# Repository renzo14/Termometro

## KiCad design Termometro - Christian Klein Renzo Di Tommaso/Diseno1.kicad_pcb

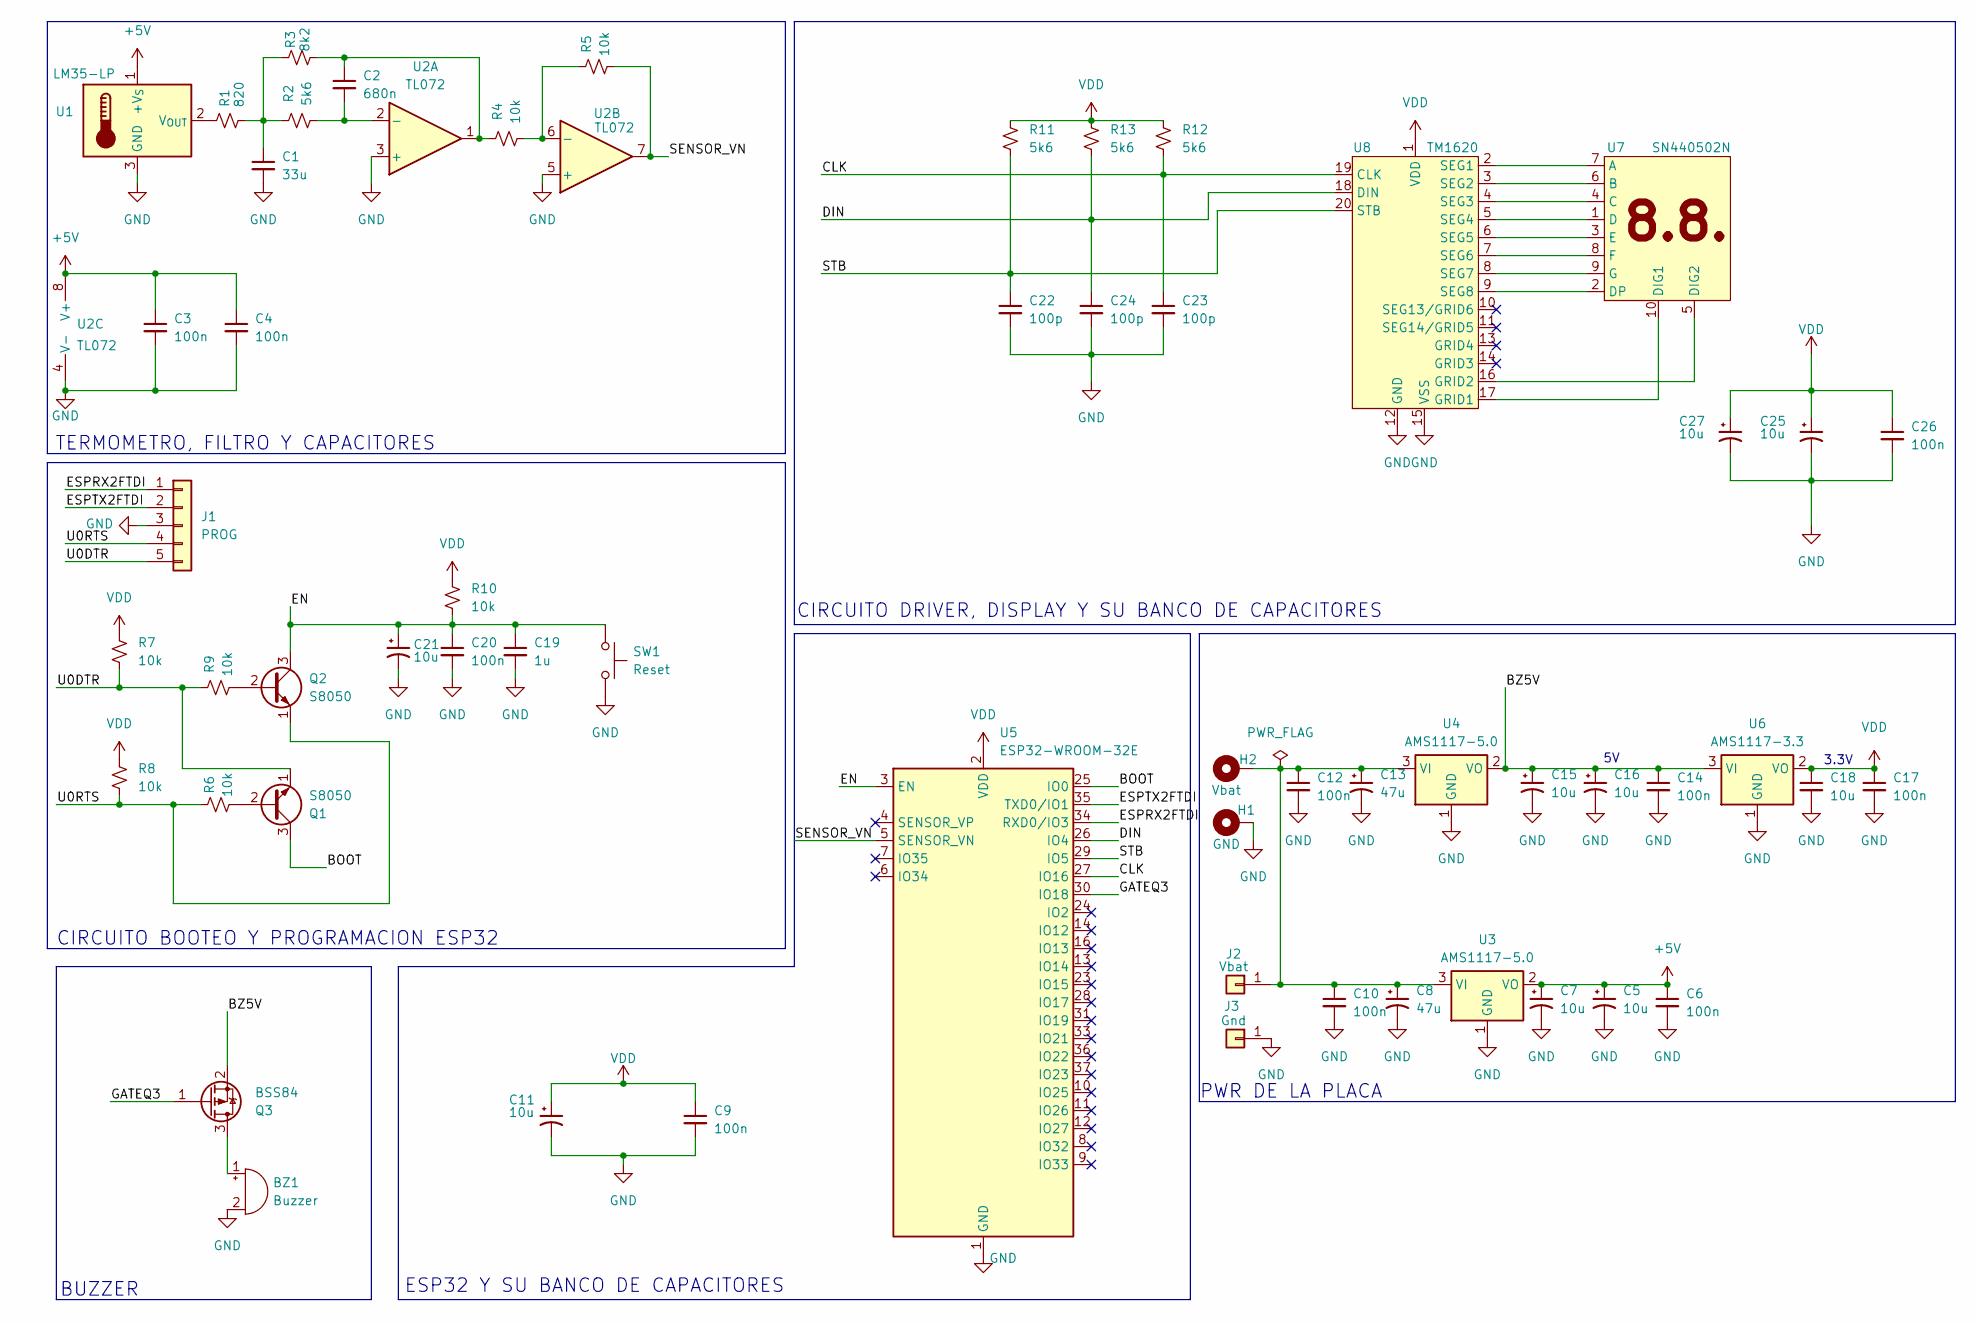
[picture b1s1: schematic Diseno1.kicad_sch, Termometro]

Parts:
BZ1: Buzzer; Buzzer_12x9.5RM7.6
C1: 33u; C_0805_2012Metric
C2: 680n; C_0603_1608Metric
C3, C4, C6, C9, C10, C12, C14, C17, C20, C26: 100n; C_0603_1608Metric
C5, C7, C11, C15, C16, C18, C21, C25, C27: 10u; C_0603_1608Metric
C8, C13: 47u; C_0805_2012Metric
C19: 1u; C_0603_1608Metric
C22, C23, C24: 100p; C_0603_1608Metric
H1: GND; MountingHole_2.2mm_M2_ISO7380_Pad
H2: Vbat; MountingHole_2.2mm_M2_ISO7380_Pad
J1: PROG; PinHeader_1x05_P2.54mm_Vertical
J2: Vbat; PinHeader_1x01_P2.54mm_Vertical
J3: Gnd; PinHeader_1x01_P2.54mm_Vertical
Q1, Q2: S8050; SOT-23
Q3: BSS84; SOT-23
R1: 820; R_0603_1608Metric
R2, R11, R12, R13: 5k6; R_0603_1608Metric
R3: 8k2; R_0603_1608Metric
R4, R5, R6, R7, R8, R9, R10: 10k; R_0603_1608Metric
SW1: Reset; SW_SPST_PTS645
U1: LM35-LP; TO-92_Inline
U2: TL072; SOIC-8_3.9x4.9mm_P1.27mm
U3, U4: AMS1117-5.0; SOT-223
U5: ESP32-WROOM-32E; ESP32-WROOM-32D
U6: AMS1117-3.3; SOT-223
U7: SN440502N; DISPLAYLEDS
U8: TM1620; SOIC-20W_7.5x12.8mm_P1.27mm

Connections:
+5V: C3.1, C4.1, C5.1, C6.1, C7.1, U1.1 (+V_{S}), U2.8 (V+), U3.2 (VO)
/BOOT: Q1.3 (C), U5.25 (IO0)
/BZ: C14.1, C15.1, C16.1, Q3.2 (S), U4.2 (VO), U6.3 (VI)
/CLK: C23.1, R12.1, U5.27 (IO16), U8.19 (CLK)
/DIN: C24.1, R13.1, U5.26 (IO4), U8.18 (DIN)
/EN: C19.1, C20.1, C21.1, Q2.3 (C), R10.1, SW1.1, U5.3 (EN)
/ESPRX2FTDI: J1.1, U5.34 (RXD0/IO3)
/ESPTX2FTDI: J1.2, U5.35 (TXD0/IO1)
/GATEQ3: Q3.1 (G), U5.30 (IO18)
/SENSOR_VN: R5.2, U2.7, U5.5 (SENSOR_VN)
/STB: C22.1, R11.1, U5.29 (IO5), U8.20 (STB)
/U0DTR: J1.5, Q1.1 (E), R7.1, R9.1
/U0RTS: J1.4, Q2.1 (E), R6.1, R8.1
GND: BZ1.2 (-), C1.2, C3.2, C4.2, C5.2, C6.2, C7.2, C8.2, C9.2, C10.2, C11.2, C12.2, C13.2, C14.2, C15.2, C16.2, C17.2, C18.2, C19.2, C20.2, C21.2, C22.2, C23.2, C24.2, C25.2, C26.2, C27.2, H1.1, J1.3, J3.1, SW1.2, U1.3 (GND), U2.3 (+), U2.4 (V-), U2.5 (+), U3.1 (GND), U4.1 (GND), U5.1 (GND), U5.15 (GND), U5.38 (GND), U5.39 (GND), U6.1 (GND), U8.12 (GND), U8.15 (VSS)
unnamed: BZ1.1 (+), Q3.3 (D)
unnamed: C1.1, R1.2, R2.1, R3.1
unnamed: C2.1, R3.2, R4.1, U2.1
unnamed: C8.1, C10.1, C12.1, C13.1, H2.1, J2.1, U3.3 (VI), U4.3 (VI)
unnamed: Q1.2 (B), R6.2
unnamed: Q2.2 (B), R9.2
unnamed: R1.1, U1.2 (V_{OUT})
unnamed: C2.2, R2.2, U2.2 (-)
unnamed: R4.2, R5.1, U2.6 (-)
unnamed: U7.7 (A), U8.2 (SEG1)
unnamed: U7.6 (B), U8.3 (SEG2)
unnamed: U7.4 (C), U8.4 (SEG3)
unnamed: U7.1 (D), U8.5 (SEG4)
unnamed: U7.10 (DIG1), U8.17 (GRID1)
unnamed: U7.5 (DIG2), U8.16 (GRID2)
unnamed: U7.2 (DP), U8.9 (SEG8)
unnamed: U7.3 (E), U8.6 (SEG5)
unnamed: U7.8 (F), U8.7 (SEG6)
unnamed: U7.9 (G), U8.8 (SEG7)
VDD: C9.1, C11.1, C17.1, C18.1, C25.1, C26.1, C27.1, R7.2, R8.2, R10.2, R11.2, R12.2, R13.2, U5.2 (VDD), U6.2 (VO), U8.1 (VDD)

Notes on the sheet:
TERMOMETRO, FILTRO Y CAPACITORES
PWR DE LA PLACA
CIRCUITO BOOTEO Y PROGRAMACION ESP32
CIRCUITO DRIVER, DISPLAY Y SU BANCO DE CAPACITORES
BUZZER
ESP32 Y SU BANCO DE CAPACITORES
3.3V

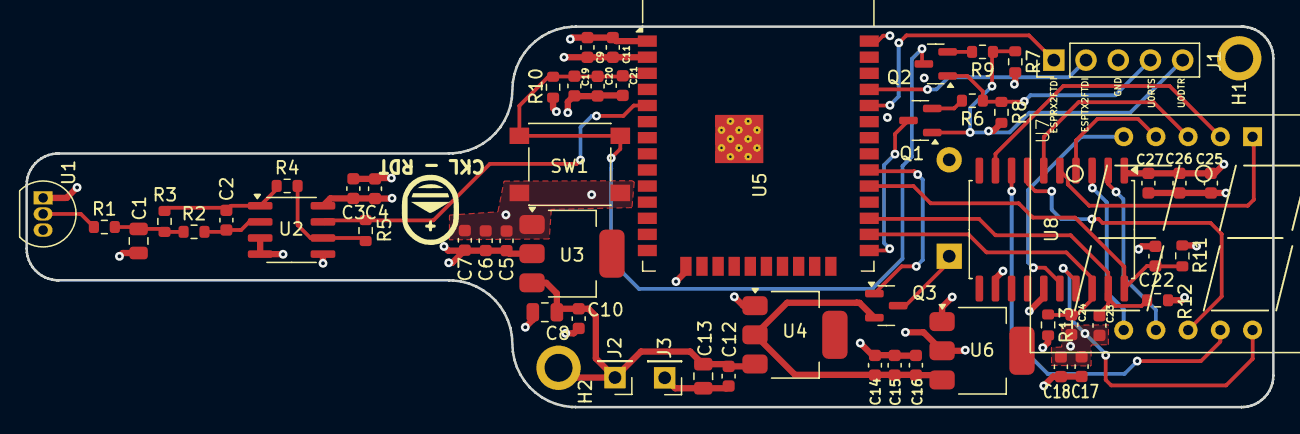
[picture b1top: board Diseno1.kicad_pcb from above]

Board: 4 copper layers, 98.3 x 30.0 mm, 58 parts (1 on the bottom side), 34 nets.
